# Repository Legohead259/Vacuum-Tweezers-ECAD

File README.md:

# Vacuum-Tweezers-ECAD
KiCAD repository for the electrical designs for the SL_ST vacuum tweezer design

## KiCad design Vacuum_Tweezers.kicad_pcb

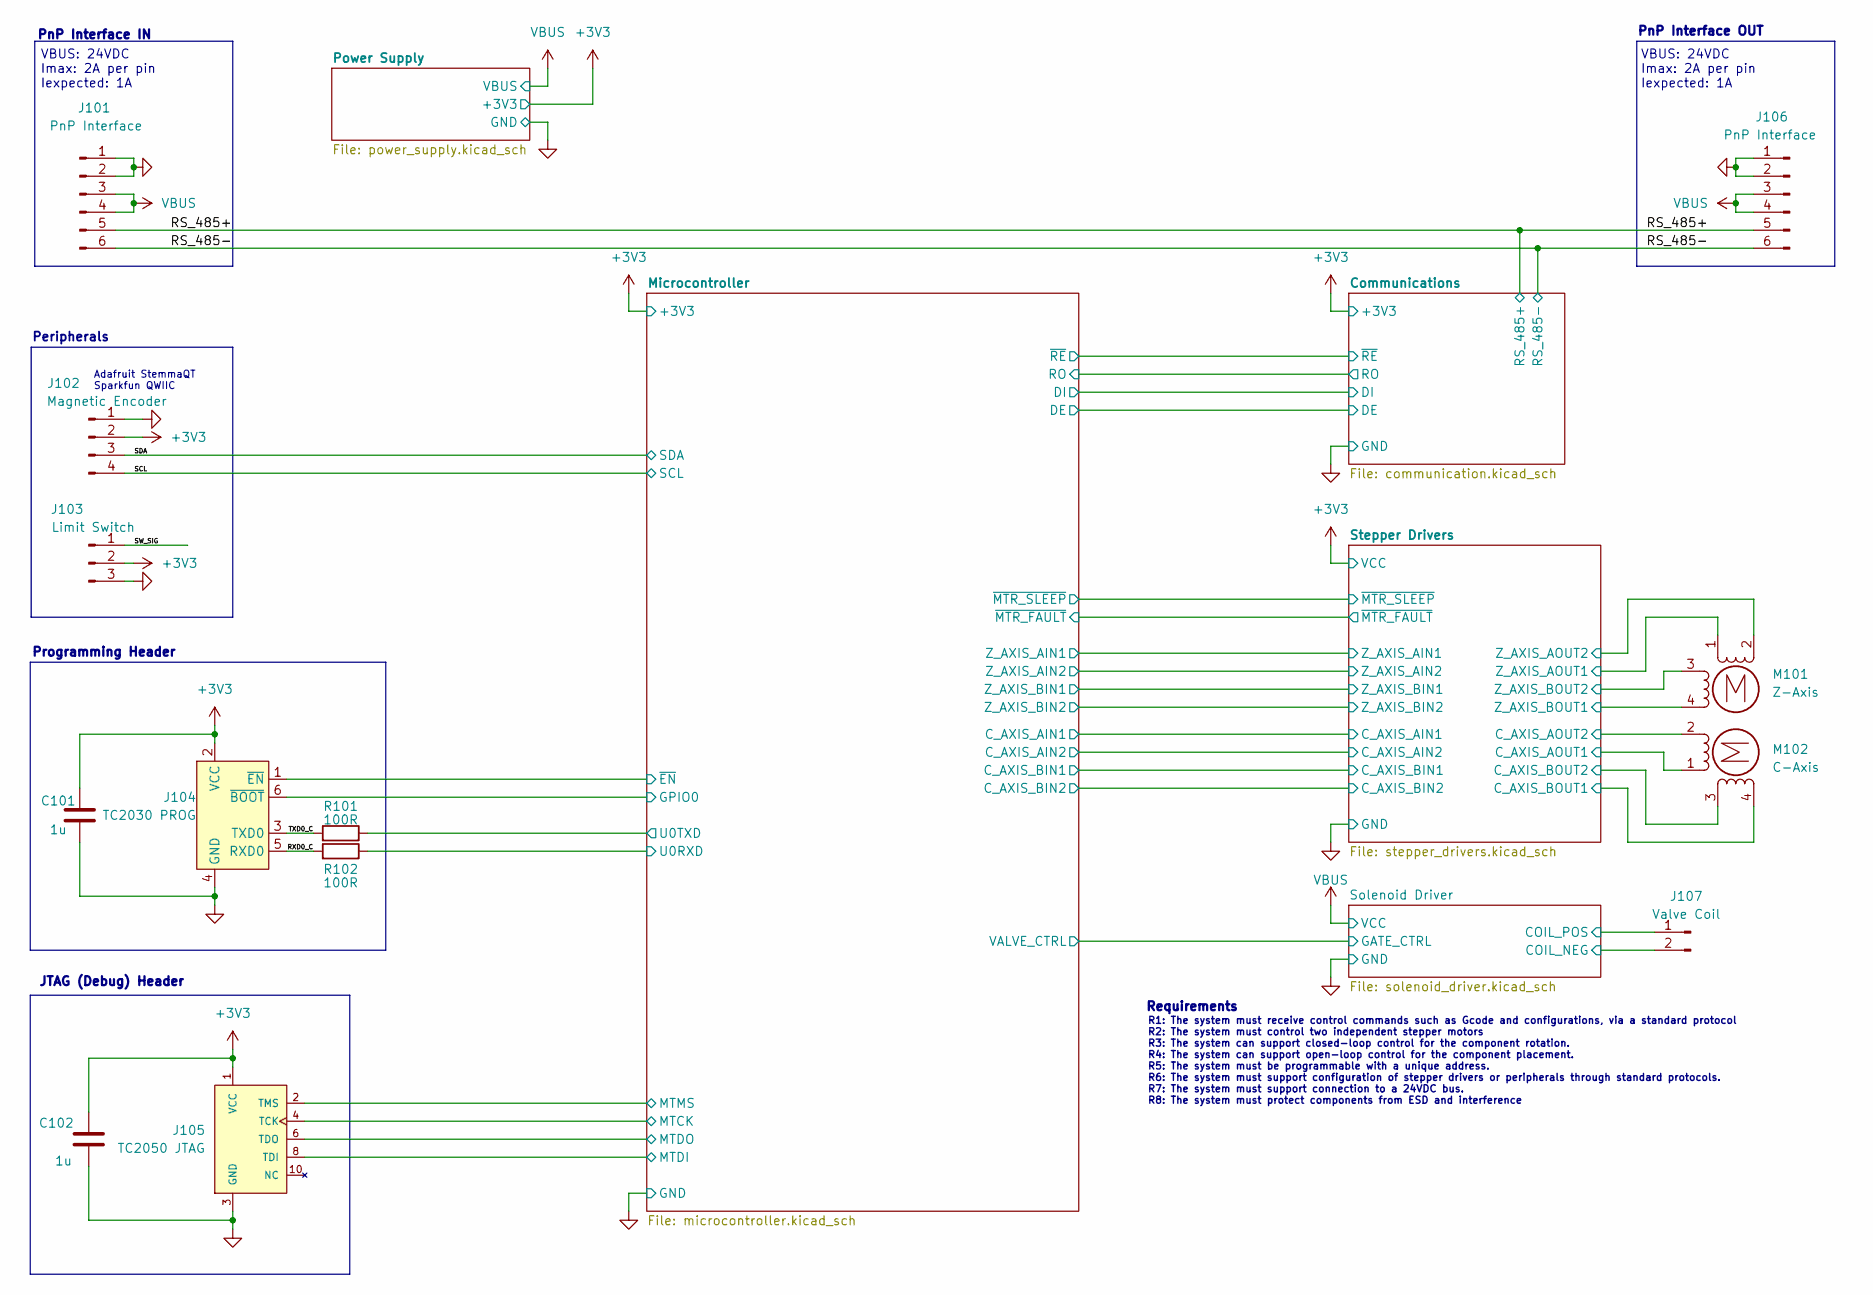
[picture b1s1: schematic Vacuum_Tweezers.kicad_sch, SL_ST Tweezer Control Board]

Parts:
C101, C102: 1u; C_0603_1608Metric
J101, J106: PnP Interface; JST_PH_S6B-PH-SM4-TB_1x06-1MP_P2.00mm_Horizontal
J102: Magnetic Encoder; JST_SH_SM04B-SRSS-TB_1x04-1MP_P1.00mm_Horizontal
J103: Limit Switch; JST_SH_SM03B-SRSS-TB_1x03-1MP_P1.00mm_Horizontal
J104: TC2030 PROG; Tag-Connect_TC2030-IDC-FP_2x03_P1.27mm_Vertical
J105: TC2050 JTAG; Tag-Connect_TC2050-IDC-FP_2x05_P1.27mm_Vertical; PARTREV A
J107: Valve Coil; JST_SH_SM02B-SRSS-TB_1x02-1MP_P1.00mm_Horizontal
M101: Z-Axis; Molex_PicoBlade_53261-0471_1x04-1MP_P1.25mm_Horizontal
M102: C-Axis; Molex_PicoBlade_53261-0471_1x04-1MP_P1.25mm_Horizontal
R101, R102: 100R; R_0603_1608Metric

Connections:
+3V3: C101.1, C102.1, J102.2, J103.2, J104.2 (VCC), J105.1 (VCC); also elsewhere on the board
/Microcontroller/GPIO0: J104.6 (~BOOT); also elsewhere on the board
/Microcontroller/MTCK: J105.4 (TCK); also elsewhere on the board
/Microcontroller/MTDI: J105.8 (TDI); also elsewhere on the board
/Microcontroller/MTDO: J105.6 (TDO); also elsewhere on the board
/Microcontroller/MTMS: J105.2 (TMS); also elsewhere on the board
/Microcontroller/U0RXD: R102.1; also elsewhere on the board
/Microcontroller/U0TXD: R101.1; also elsewhere on the board
/Microcontroller/~EN: J104.1 (~EN); also elsewhere on the board
/RS_485+: J101.5, J106.5; also elsewhere on the board
/RS_485-: J101.6, J106.6; also elsewhere on the board
/RXD0_C: J104.5 (RXD0), R102.2
/SCL: J102.4; also elsewhere on the board
/SDA: J102.3; also elsewhere on the board
/SW_SIG: J103.1
/Solenoid Driver/COIL_NEG: J107.2; also elsewhere on the board
/Solenoid Driver/COIL_POS: J107.1; also elsewhere on the board
/Stepper Drivers/C_AXIS_AOUT1: M102.1; also elsewhere on the board
/Stepper Drivers/C_AXIS_AOUT2: M102.2 (-); also elsewhere on the board
/Stepper Drivers/C_AXIS_BOUT1: M102.4; also elsewhere on the board
/Stepper Drivers/C_AXIS_BOUT2: M102.3; also elsewhere on the board
/Stepper Drivers/Z_AXIS_AOUT1: M101.1; also elsewhere on the board
/Stepper Drivers/Z_AXIS_AOUT2: M101.2 (-); also elsewhere on the board
/Stepper Drivers/Z_AXIS_BOUT1: M101.4; also elsewhere on the board
/Stepper Drivers/Z_AXIS_BOUT2: M101.3; also elsewhere on the board
/TXD0_C: J104.3 (TXD0), R101.2
GND: C101.2, C102.2, J101.1, J101.2, J102.1, J103.3, J104.4 (GND), J105.3 (GND), J105.5 (GND), J105.7 (GND), J105.9 (GND), J106.1, J106.2; also elsewhere on the board
VBUS: J101.3, J101.4, J106.3, J106.4; also elsewhere on the board

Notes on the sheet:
Peripherals
Requirements
JTAG (Debug) Header
Programming Header
VBUS: 24VDC Imax: 2A per pin Iexpected: 1A
PnP Interface OUT
R1: The system must receive control commands such as Gcode and configurations, via a standard protocol R2: The system must control two independent stepper motors R3: The system can support closed-loop control for the component rotation. R4: The system can support open-loop control for the component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
PnP Interface IN
Adafruit StemmaQT Sparkfun QWIIC

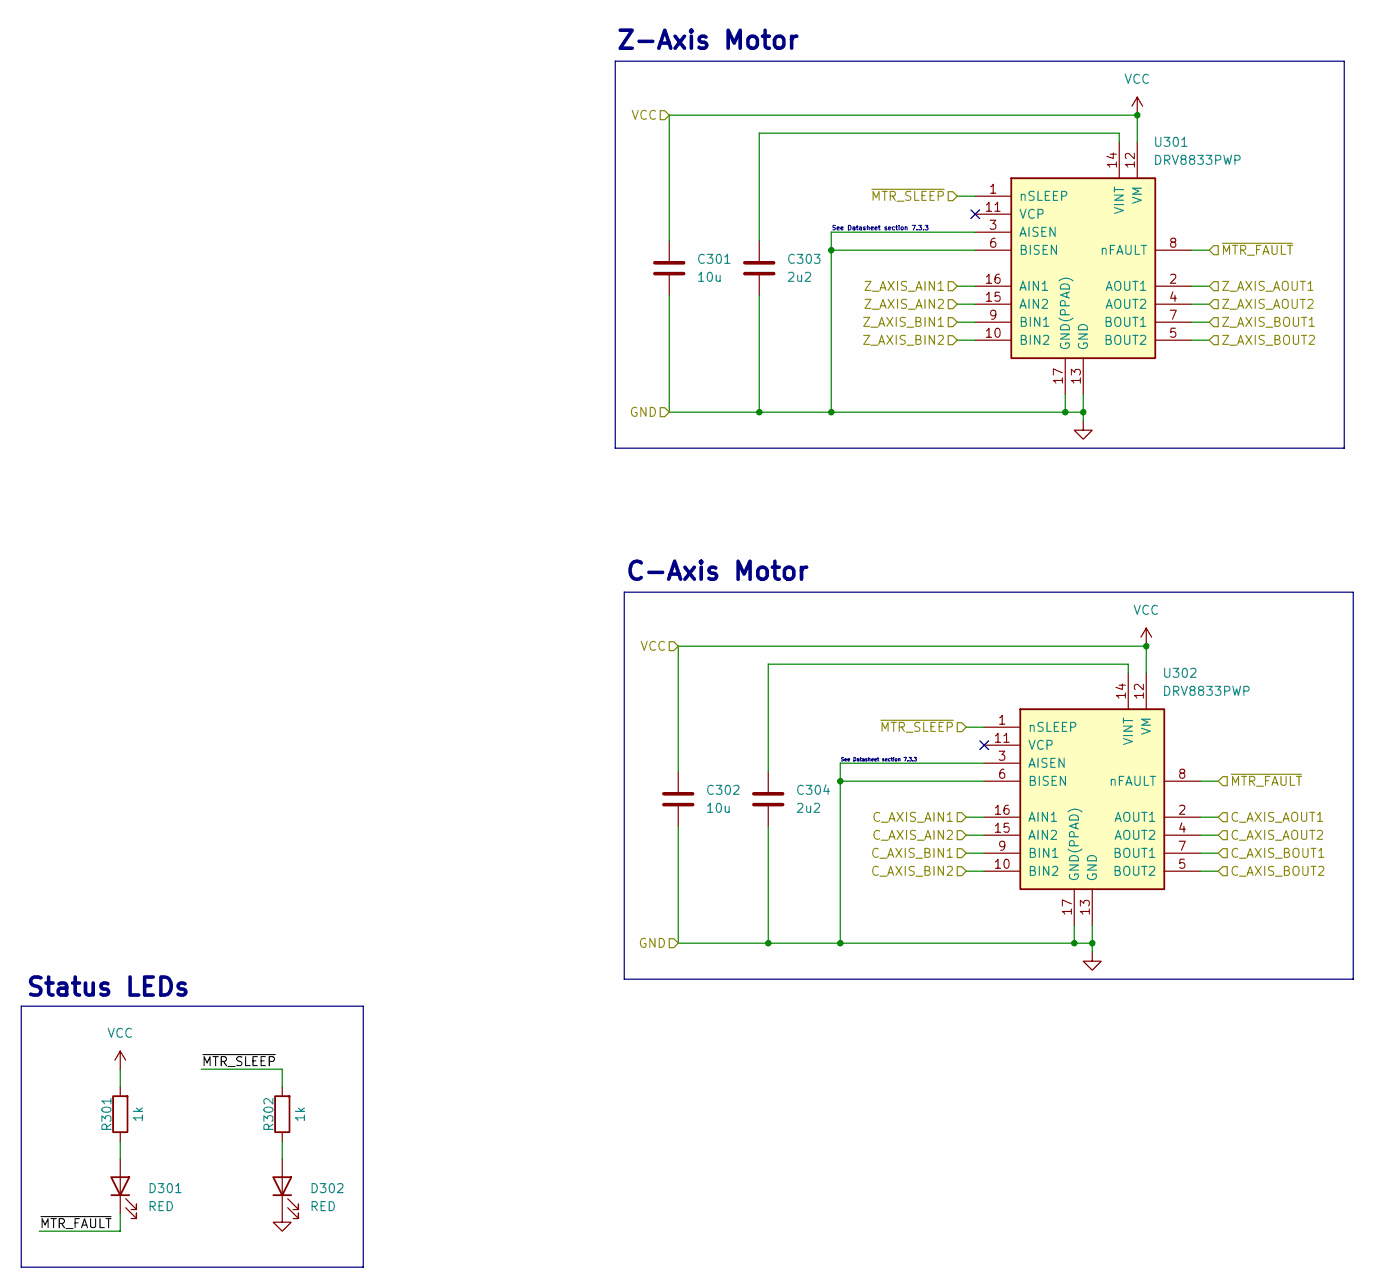
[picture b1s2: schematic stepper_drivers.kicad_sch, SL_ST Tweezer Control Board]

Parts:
C301, C302: 10u; C_0603_1608Metric
C303, C304: 2u2; C_0603_1608Metric
D301, D302: RED; LED_0603_1608Metric
R301, R302: 1k; R_0603_1608Metric
U301, U302: DRV8833PWP; HTSSOP-16-1EP_4.4x5mm_P0.65mm_EP3.4x5mm_Mask2.46x2.31mm_The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

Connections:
+3V3: C301.1, C302.1, R301.2, U301.12 (VM), U302.12 (VM); also elsewhere on the board
/Microcontroller/C_AXIS_AIN1: U302.16 (AIN1); also elsewhere on the board
/Microcontroller/C_AXIS_AIN2: U302.15 (AIN2); also elsewhere on the board
/Microcontroller/C_AXIS_BIN1: U302.9 (BIN1); also elsewhere on the board
/Microcontroller/C_AXIS_BIN2: U302.10 (BIN2); also elsewhere on the board
/Microcontroller/Z_AXIS_AIN1: U301.16 (AIN1); also elsewhere on the board
/Microcontroller/Z_AXIS_AIN2: U301.15 (AIN2); also elsewhere on the board
/Microcontroller/Z_AXIS_BIN1: U301.9 (BIN1); also elsewhere on the board
/Microcontroller/Z_AXIS_BIN2: U301.10 (BIN2); also elsewhere on the board
/Stepper Drivers/C_AXIS_AOUT1: U302.2 (AOUT1); also elsewhere on the board
/Stepper Drivers/C_AXIS_AOUT2: U302.4 (AOUT2); also elsewhere on the board
/Stepper Drivers/C_AXIS_BOUT1: U302.7 (BOUT1); also elsewhere on the board
/Stepper Drivers/C_AXIS_BOUT2: U302.5 (BOUT2); also elsewhere on the board
/Stepper Drivers/Z_AXIS_AOUT1: U301.2 (AOUT1); also elsewhere on the board
/Stepper Drivers/Z_AXIS_AOUT2: U301.4 (AOUT2); also elsewhere on the board
/Stepper Drivers/Z_AXIS_BOUT1: U301.7 (BOUT1); also elsewhere on the board
/Stepper Drivers/Z_AXIS_BOUT2: U301.5 (BOUT2); also elsewhere on the board
/Stepper Drivers/~MTR_FAULT: D301.1 (K), U301.8 (nFAULT), U302.8 (nFAULT); also elsewhere on the board
/Stepper Drivers/~MTR_SLEEP: R302.2, U301.1 (nSLEEP), U302.1 (nSLEEP); also elsewhere on the board
GND: C301.2, C302.2, C303.2, C304.2, D302.1 (K), U301.3 (AISEN), U301.6 (BISEN), U301.13 (GND), U301.17 (GND(PPAD)), U302.3 (AISEN), U302.6 (BISEN), U302.13 (GND), U302.17 (GND(PPAD)); also elsewhere on the board
unnamed: D301.2 (A), R301.1
unnamed: D302.2 (A), R302.1
unnamed: C303.1, U301.14 (VINT)
unnamed: C304.1, U302.14 (VINT)

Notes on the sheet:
See Datasheet section 7.3.3
Status LEDs
C-Axis Motor
Z-Axis Motor

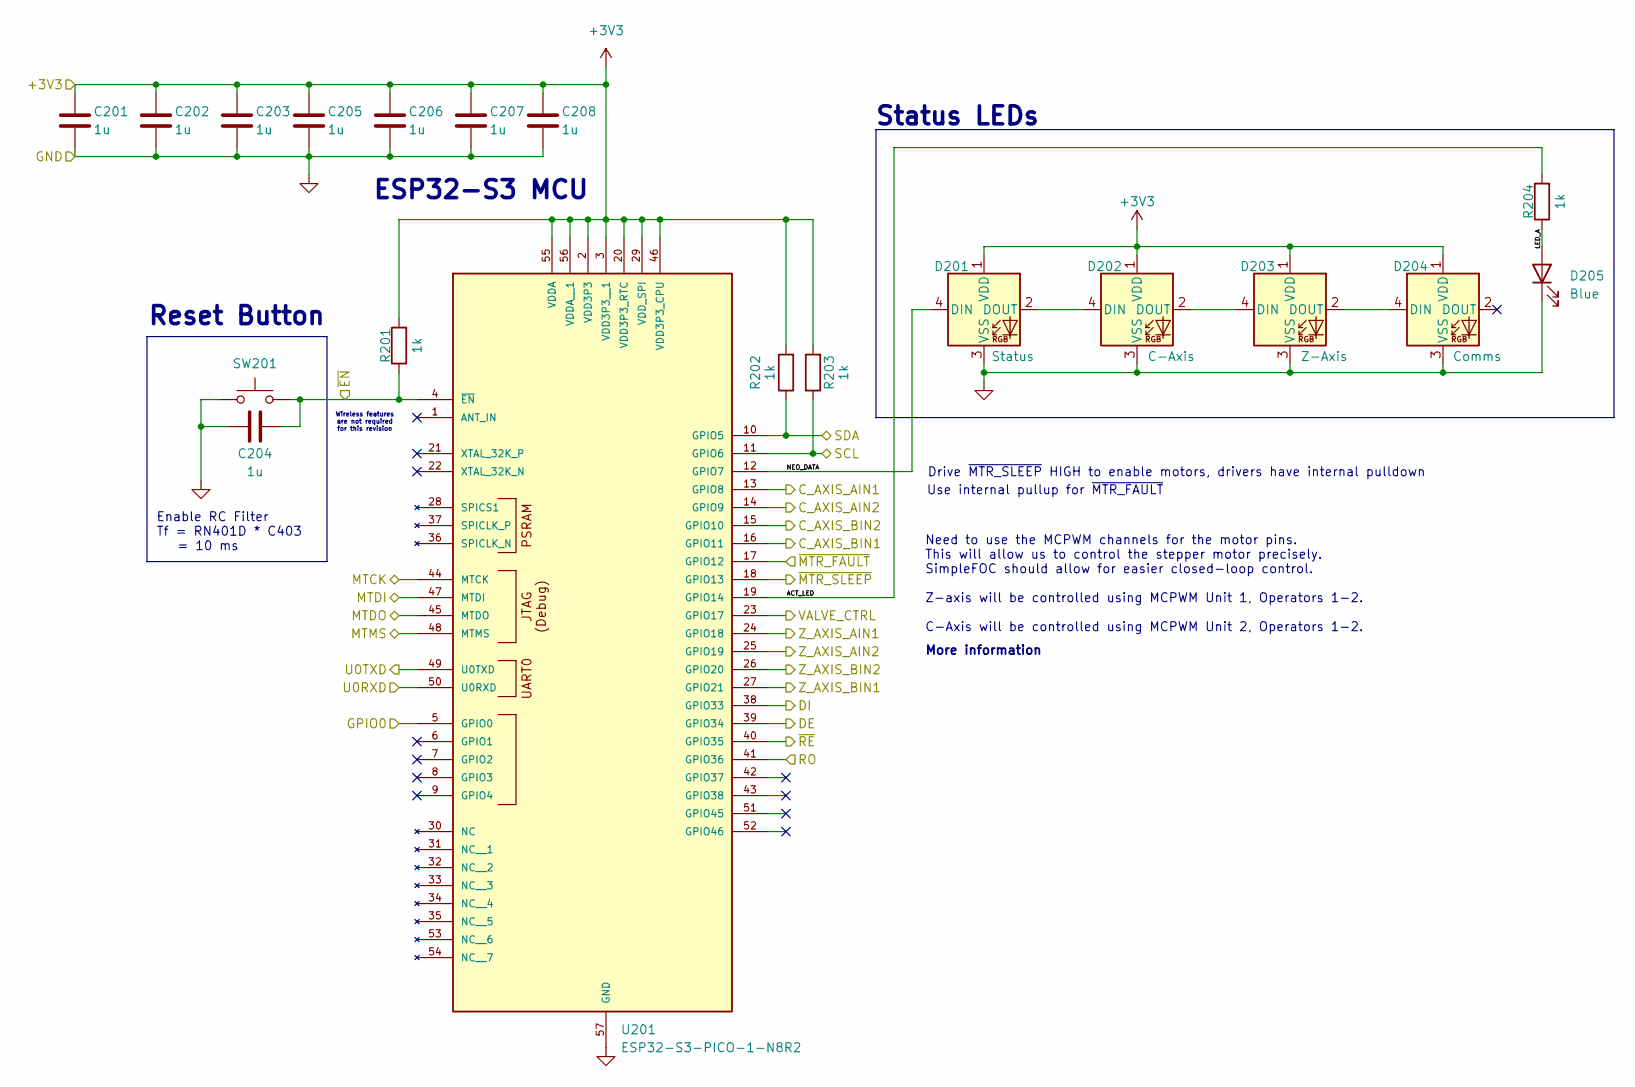
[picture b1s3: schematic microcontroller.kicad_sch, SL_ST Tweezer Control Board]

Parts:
C201, C202, C203, C204, C205, C206, C207, C208: 1u; C_0603_1608Metric
D201: Status; LED_WS2812B-2020_PLCC4_2.0x2.0mm
D202: C-Axis; LED_WS2812B-2020_PLCC4_2.0x2.0mm
D203: Z-Axis; LED_WS2812B-2020_PLCC4_2.0x2.0mm
D204: Comms; LED_WS2812B-2020_PLCC4_2.0x2.0mm
D205: Blue; LED_0603_1608Metric
R201, R202, R203, R204: 1k; R_0603_1608Metric
SW201: SW_Push; SW_Push_1P1T-SH_NO_CK_KMR2xxG
U201: ESP32-S3-PICO-1-N8R2; PQFN40P700X700X106-57N; PARTREV 1.0

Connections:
+3V3: C201.1, C202.1, C203.1, C205.1, C206.1, C207.1, C208.1, D201.1 (VDD), D202.1 (VDD), D203.1 (VDD), D204.1 (VDD), R201.2, R202.2, R203.2, U201.2 (VDD3P3), U201.3 (VDD3P3__1), U201.20 (VDD3P3_RTC), U201.29 (VDD_SPI), U201.46 (VDD3P3_CPU), U201.55 (VDDA), U201.56 (VDDA__1); also elsewhere on the board
/Communications/DE: U201.39 (GPIO34); also elsewhere on the board
/Communications/DI: U201.38 (GPIO33); also elsewhere on the board
/Communications/RO: U201.41 (GPIO36); also elsewhere on the board
/Communications/~RE: U201.40 (GPIO35); also elsewhere on the board
/Microcontroller/ACT_LED: R204.2, U201.19 (GPIO14)
/Microcontroller/C_AXIS_AIN1: U201.13 (GPIO8); also elsewhere on the board
/Microcontroller/C_AXIS_AIN2: U201.14 (GPIO9); also elsewhere on the board
/Microcontroller/C_AXIS_BIN1: U201.16 (GPIO11); also elsewhere on the board
/Microcontroller/C_AXIS_BIN2: U201.15 (GPIO10); also elsewhere on the board
/Microcontroller/GPIO0: U201.5 (GPIO0); also elsewhere on the board
/Microcontroller/LED_A: D205.2 (A), R204.1
/Microcontroller/MTCK: U201.44 (MTCK); also elsewhere on the board
/Microcontroller/MTDI: U201.47 (MTDI); also elsewhere on the board
/Microcontroller/MTDO: U201.45 (MTDO); also elsewhere on the board
/Microcontroller/MTMS: U201.48 (MTMS); also elsewhere on the board
/Microcontroller/NEO_DATA: D201.4 (DIN), U201.12 (GPIO7)
/Microcontroller/U0RXD: U201.50 (U0RXD); also elsewhere on the board
/Microcontroller/U0TXD: U201.49 (U0TXD); also elsewhere on the board
/Microcontroller/VALVE_CTRL: U201.23 (GPIO17); also elsewhere on the board
/Microcontroller/Z_AXIS_AIN1: U201.24 (GPIO18); also elsewhere on the board
/Microcontroller/Z_AXIS_AIN2: U201.25 (GPIO19); also elsewhere on the board
/Microcontroller/Z_AXIS_BIN1: U201.27 (GPIO21); also elsewhere on the board
/Microcontroller/Z_AXIS_BIN2: U201.26 (GPIO20); also elsewhere on the board
/Microcontroller/~EN: C204.1, R201.1, SW201.2, U201.4 (~EN); also elsewhere on the board
/SCL: R203.1, U201.11 (GPIO6); also elsewhere on the board
/SDA: R202.1, U201.10 (GPIO5); also elsewhere on the board
/Stepper Drivers/~MTR_FAULT: U201.17 (GPIO12); also elsewhere on the board
/Stepper Drivers/~MTR_SLEEP: U201.18 (GPIO13); also elsewhere on the board
GND: C201.2, C202.2, C203.2, C204.2, C205.2, C206.2, C207.2, C208.2, D201.3 (VSS), D202.3 (VSS), D203.3 (VSS), D204.3 (VSS), D205.1 (K), SW201.1, U201.57 (GND); also elsewhere on the board
unnamed: D201.2 (DOUT), D202.4 (DIN)
unnamed: D202.2 (DOUT), D203.4 (DIN)
unnamed: D203.2 (DOUT), D204.4 (DIN)

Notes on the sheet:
Use internal pullup for ~{MTR_FAULT}
Enable RC Filter Tf = RN401D * C403 = 10 ms
More information
Reset Button
Wireless features are not required for this revision
Status LEDs
Drive ~{MTR_SLEEP} HIGH to enable motors, drivers have internal pulldown
ESP32-S3 MCU
Need to use the MCPWM channels for the motor pins. This will allow us to control the stepper motor precisely. SimpleFOC should allow for easier closed-loop control. Z-axis will be controlled using MCPWM Unit 1, Operators 1-2. C-Axis will be controlled using MCPWM Unit 2, Operators 1-2.

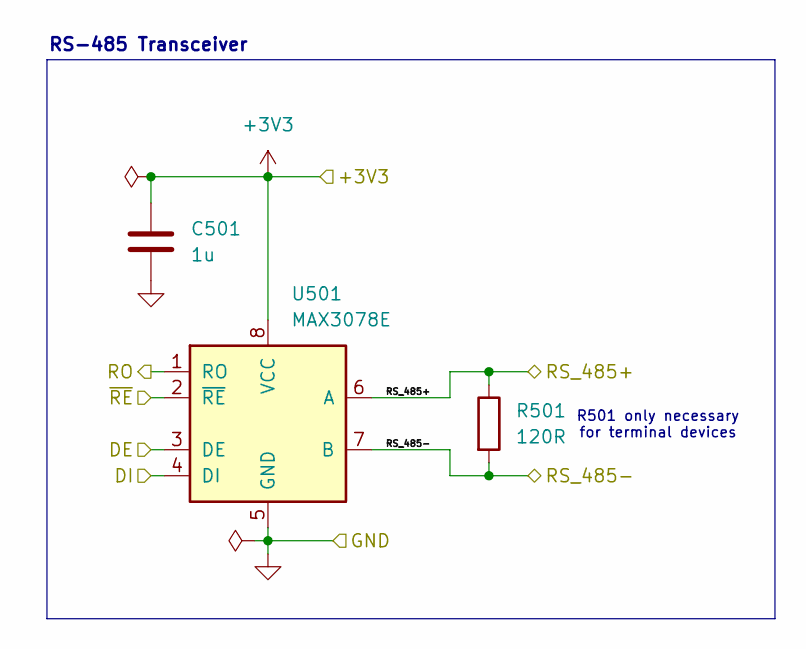
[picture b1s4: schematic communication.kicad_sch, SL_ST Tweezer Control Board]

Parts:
C501: 1u; C_0603_1608Metric
R501: 120R; R_0603_1608Metric
U501: MAX3078E; SOIC-8_3.9x4.9mm_P1.27mm

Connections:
+3V3: C501.1, U501.8 (VCC); also elsewhere on the board
/Communications/DE: U501.3 (DE); also elsewhere on the board
/Communications/DI: U501.4 (DI); also elsewhere on the board
/Communications/RO: U501.1 (RO); also elsewhere on the board
/Communications/~RE: U501.2 (~RE); also elsewhere on the board
/RS_485+: R501.1, U501.6 (A); also elsewhere on the board
/RS_485-: R501.2, U501.7 (B); also elsewhere on the board
GND: C501.2, U501.5 (GND); also elsewhere on the board

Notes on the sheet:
R501 only necessary for terminal devices
RS-485 Transceiver

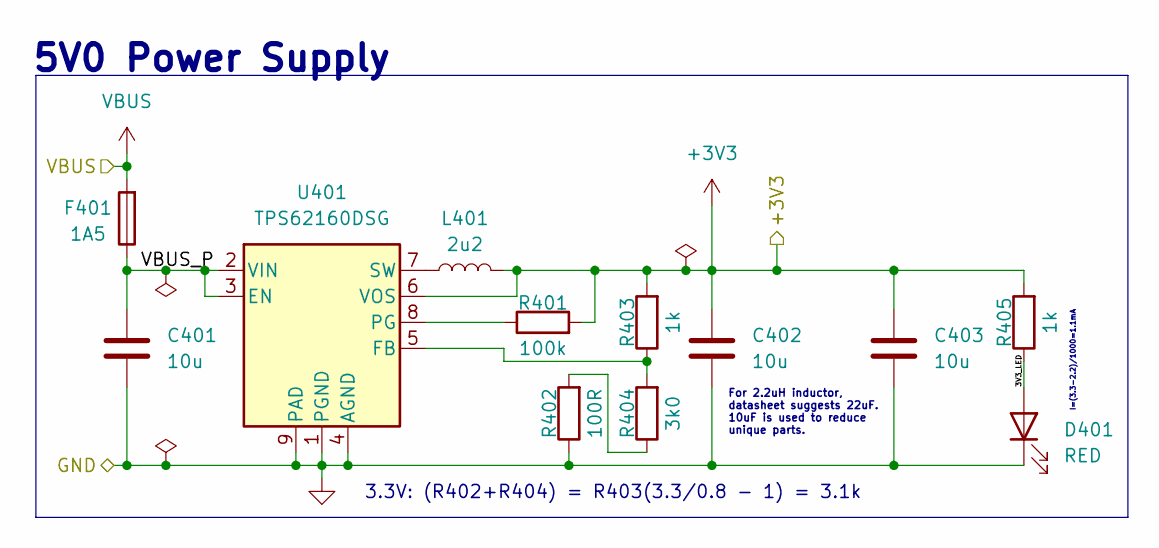
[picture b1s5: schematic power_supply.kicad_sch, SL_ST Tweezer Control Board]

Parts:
C401, C402, C403: 10u; C_0603_1608Metric
D401: RED; LED_0603_1608Metric
F401: 1A5; Fuseholder_Littelfuse_Nano2_154x
L401: 2u2; L_Coilcraft_XFL2010
R401: 100k; R_0603_1608Metric
R402: 100R; R_0603_1608Metric
R403, R405: 1k; R_0603_1608Metric
R404: 3k0; R_0603_1608Metric
U401: TPS62160DSG; WSON-8-1EP_2x2mm_P0.5mm_EP0.9x1.6mm_ThermalVias

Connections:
+3V3: C402.1, C403.1, L401.2, R401.2, R403.2, R405.2, U401.6 (VOS); also elsewhere on the board
/Power Supply/3V3_LED: D401.2 (A), R405.1
/Power Supply/VBUS_P: C401.1, F401.1, U401.2 (VIN), U401.3 (EN)
GND: C401.2, C402.2, C403.2, D401.1 (K), R402.1, U401.1 (PGND), U401.4 (AGND), U401.9 (PAD); also elsewhere on the board
unnamed: R402.2, R404.1
unnamed: R403.1, R404.2, U401.5 (FB)
unnamed: R401.1, U401.8 (PG)
unnamed: L401.1, U401.7 (SW)
VBUS: F401.2; also elsewhere on the board

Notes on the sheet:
I=(3.3-2.2)/1000=1.1mA
For 2.2uH inductor, datasheet suggests 22uF. 10uF is used to reduce unique parts.
5V0 Power Supply
3.3V: (R402+R404) = R403(3.3/0.8 - 1) = 3.1k

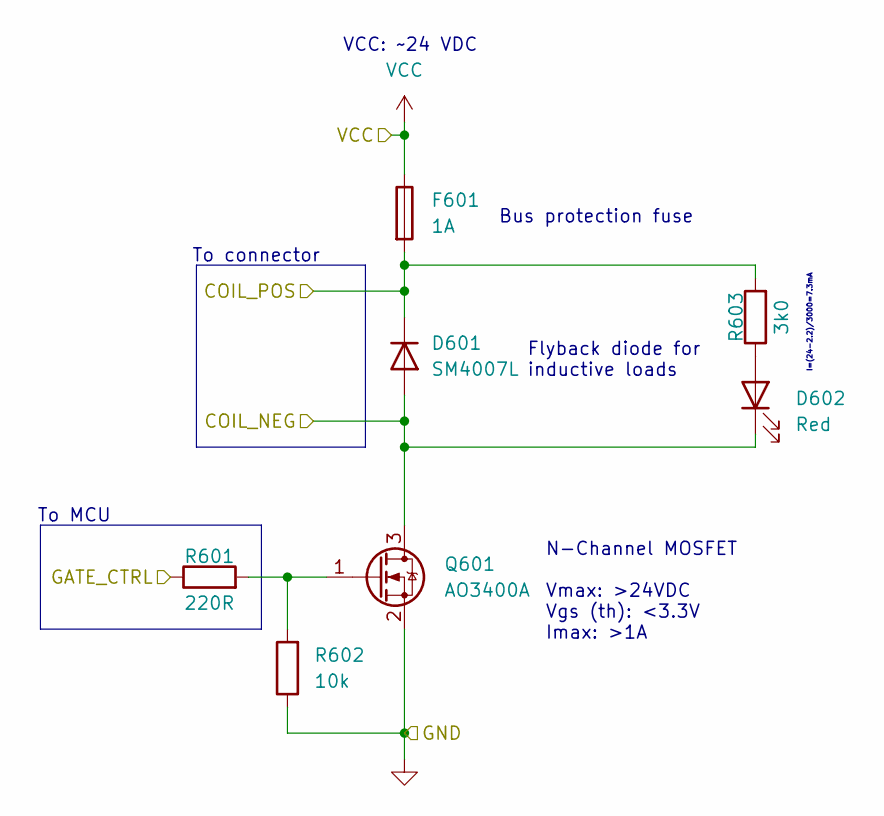
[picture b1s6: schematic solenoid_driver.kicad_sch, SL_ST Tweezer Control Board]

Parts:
D601: SM4007L; D_0603_1608Metric
D602: Red; LED_0603_1608Metric
F601: 1A; Fuseholder_Littelfuse_Nano2_154x
Q601: AO3400A; SOT-23
R601: 220R; R_0603_1608Metric
R602: 10k; R_0603_1608Metric
R603: 3k0; R_0603_1608Metric

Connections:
/Microcontroller/VALVE_CTRL: R601.1; also elsewhere on the board
/Solenoid Driver/COIL_NEG: D601.2 (A), D602.1 (K), Q601.3 (D); also elsewhere on the board
/Solenoid Driver/COIL_POS: D601.1 (K), F601.2, R603.2; also elsewhere on the board
GND: Q601.2 (S), R602.1; also elsewhere on the board
unnamed: D602.2 (A), R603.1
unnamed: Q601.1 (G), R601.2, R602.2
VBUS: F601.1; also elsewhere on the board

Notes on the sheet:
Flyback diode for inductive loads
N-Channel MOSFET Vmax: >24VDC Vgs (th): <3.3V Imax: >1A
To connector
VCC: ~24 VDC
I=(24-2.2)/3000=7.3mA
To MCU
Bus protection fuse

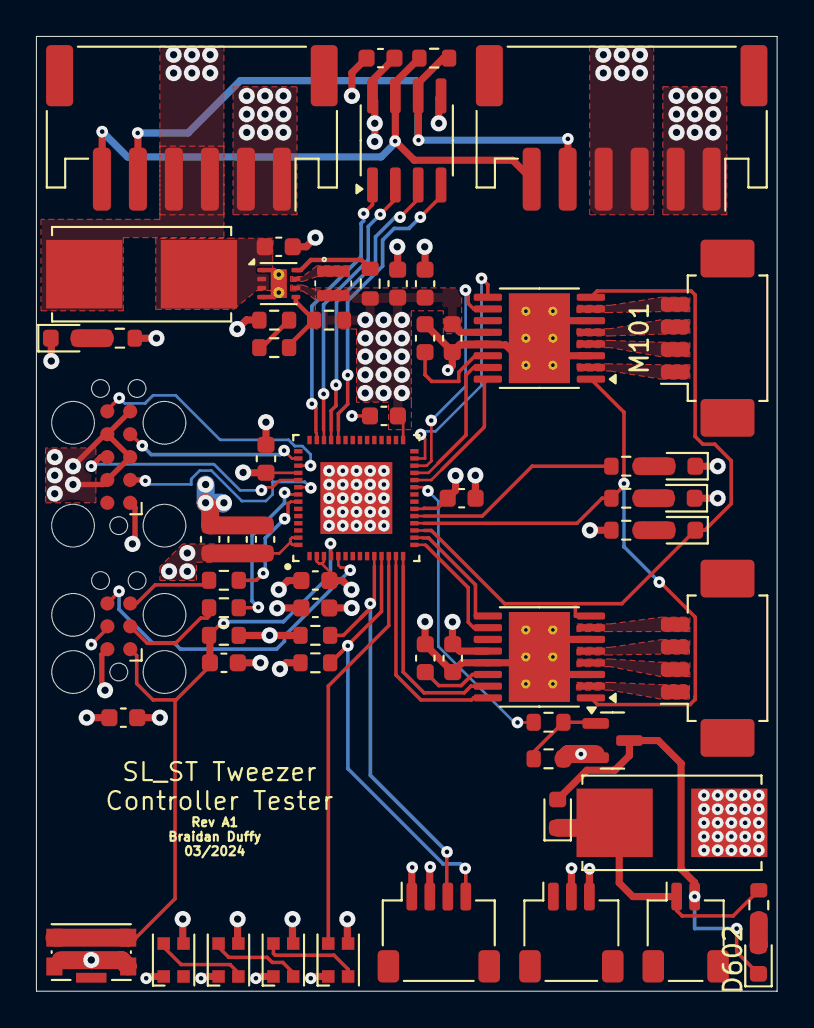
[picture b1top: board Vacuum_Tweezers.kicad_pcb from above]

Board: 4 copper layers, 41.1 x 53.0 mm, 64 parts (0 on the bottom side), 60 nets.

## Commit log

2024-03-04 Added initial Revision A1 schematic
2024-03-06 Changed motor power supply
    Removed 5V power rail. Migrated 3.3V rail to TPS62160
2024-03-06 Changed footprints
    Modified some footprints to better fit layout and part availability
2024-03-24 Finished Rev A1 PCB
    Added all components and routed parts for Rev A1 PCB
2024-03-24 Fixed footprint reference
